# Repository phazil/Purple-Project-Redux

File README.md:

# Purple Project Redux

A recreation of @TheTrain24's Purple Project seen here:
[Reference Posts](https://github.com/phazil/Purple-Project-Redux/blob/main/Docs/Inspiration%20Posts.md)

This started out as a post graduation project (someone in biology hire me pls) to explore deeper into the hobbies I was already interested in. Did all of the CAD/KiCAD work myself, and also because I missed out on the originals Train posted. Lots was learned here, and documenting it all isn't as fun as making it but I guess it's necessary lol. 

This is my attempt to recreate Train's version, however there are differences. There is no custom wiring terminal pcb, it's not double stacked FR4 for both front/back panel, and there's no usage of low profile OSBMXs. I used a right angle header soldered onto a Basic Breakout Board running GP2040-CE along with a 20-pin wiring harness. There is some soldering involved in this to get the menu panel working however it is sequential and there's only 1 ground line needed. The single panel do not flex at all with the increase inside area of the 3D prints. you would have to try to push down really hard on the center of the panels to even see any sort of flex. Any low profile buttons that fit within a 20mm tall enclosure should work too.

As regards for making and selling, I do not think this is the most efficient way to go about it. The original project I am pretty sure was scrapped due to how expensive FR4 panels end up being. Using laser cut acrylic is probably more efficient for anything of the sorts. Total cost for making 5 of these is about $750 with the materials I chose, so around $160 each is close to breaking even. This does not at all account for the time needed to print parts or build this.

If you need any help or are even thinking about making this please contact me on Discord! I'd be willing to help. @phazil

## Repository Directory:
* [Full Readme](https://github.com/phazil/Purple-Project-Redux/blob/main/README.md)
	* [Reference Posts](https://github.com/phazil/Purple-Project-Redux/blob/main/Docs/Inspiration%20Posts.md)
	* [Bill of Materials](https://github.com/phazil/Purple-Project-Redux/blob/main/Docs/Bill%20of%20Materials.md)
   	* [Ordering Panels and PCBs](https://github.com/phazil/Purple-Project-Redux/blob/main/Docs/Ordering%20Guide.md)
 	* [Printing Parts](https://github.com/phazil/Purple-Project-Redux/blob/main/Docs/Printing%20Parts.md)
	* [Rough Assembly Guide](https://github.com/phazil/Purple-Project-Redux/blob/main/Docs/Assembly%20Guide.md)
 	* [Editting Parts](https://github.com/phazil/Purple-Project-Redux/blob/main/Docs/Editting%20Parts.md)

## Features, Details, and To-Dos

### 3 Variations:
- Purple Project Redux: 35.56cm x 20.32cm x 2.32cm (14" x 8" x 0.9")
- **UNTESTED** Acrylic Layer Version: 35.56cm x 20.32cm x 2.47cm (14" x 8" x 0.97")
- Right side carrying handle modifcation available for both (Adds about 1.25" to total length)

### Features:
- Daigo-ish Layout
- Stickless+
- Bottom Rubber Pads
	- Mirrored for both sides
- Right side carrying handle
- PCB top/bottom plate (1.6mm)
- Possible Acrylic Top Plate (3.1mm total thickness, only screw ins work)
- Designed PCB Auxilliary Button Panel

Each designed part can fit in a 250x250x250 volume print bed
- 6 total pieces
	- Top Left
	- Top Right
	- Top Middle (Requires USB-C keystone jack panel mount)
	- Bottom Left
	- Bottom Middle
	- Bottom Right
- Printed in [Voron Spec](https://docs.vorondesign.com/sourcing.html#print-settings) hopefully

### To Do's:
- [x] BOM Page written
- [x] Ordering Page written
- [x] Printing Parts written
- [x] Rough Assembly Guide written
- [x] Editting Parts written
- [ ] Bottom Rubber/Foam pad DXFs

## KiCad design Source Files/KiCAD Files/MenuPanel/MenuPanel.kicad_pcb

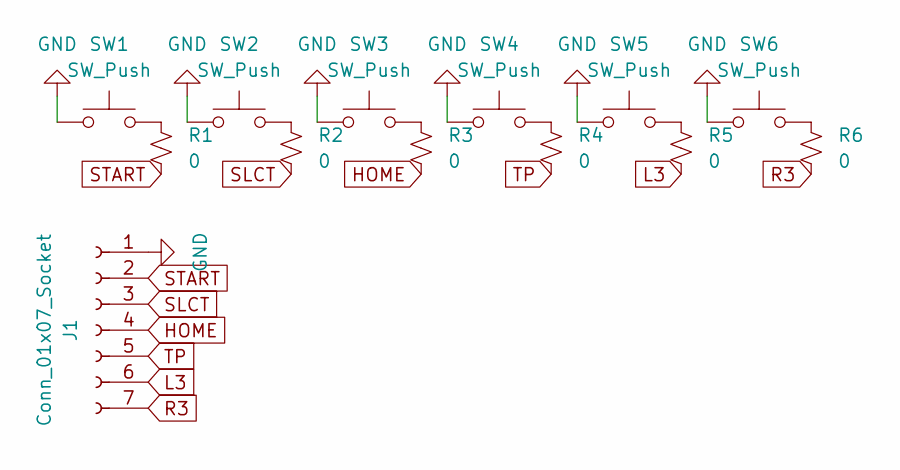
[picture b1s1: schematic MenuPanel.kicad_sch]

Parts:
J1: Conn_01x07_Socket; PinSocket_1x07_P2.54mm_Vertical
R1, R2, R3, R4, R5, R6: 0; R_0805_2012Metric_Pad1.20x1.40mm_HandSolder
SW1, SW2, SW3, SW4, SW5, SW6: SW_Push; SW_PUSH_6mm_H4.3mm

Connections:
GND: J1.1, SW1.1, SW2.1, SW3.1, SW4.1, SW5.1, SW6.1
HOME: J1.4, R3.2
L3: J1.6, R5.2
unnamed: R1.1, SW1.2
unnamed: R2.1, SW2.2
unnamed: R3.1, SW3.2
unnamed: R4.1, SW4.2
unnamed: R5.1, SW5.2
unnamed: R6.1, SW6.2
R3: J1.7, R6.2
SLCT: J1.3, R2.2
START: J1.2, R1.2
TP: J1.5, R4.2

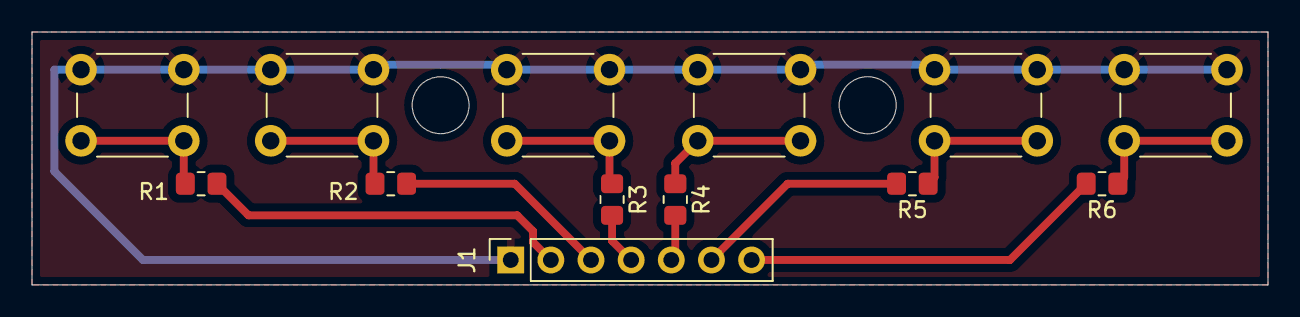
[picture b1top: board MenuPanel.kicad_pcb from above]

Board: 2 copper layers, 78.2 x 16.0 mm, 13 parts (0 on the bottom side), 13 nets.

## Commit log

2024-11-22 initial test
2024-11-23 Updated Images
2024-11-24 adding personal build pictures
